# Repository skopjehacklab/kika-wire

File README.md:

Our version of the Little Wire[1] board.

This is a KiCAD project. Pictures of the finished board can be found at : https://i.imgur.com/Hss5jGV.jpg and https://i.imgur.com/ivjp6nn.jpg

[1] - http://littlewire.cc/

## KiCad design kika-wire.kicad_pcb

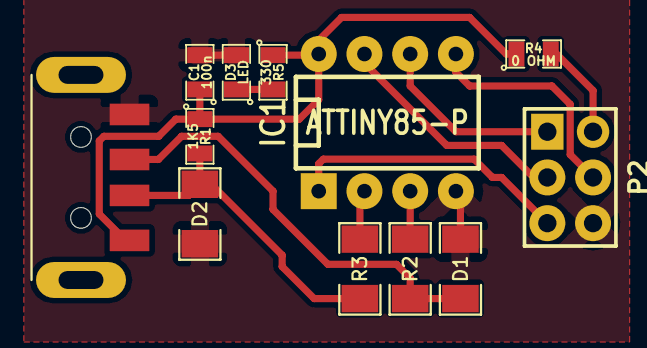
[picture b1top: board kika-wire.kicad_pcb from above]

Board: 2 copper layers, 12 parts (0 on the bottom side), 12 nets.

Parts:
C1: 100n; SM0805
D1, D2: 3V6; SM1206
D3: LED; SM0805
IC1: ATTINY85-P; DIP-8__300
P1: USB-A; USB-A-PLUG-SMT
P2: CONN_3X2; pin_array_3x2
R1: 1K5; SM0805
R2, R3: 68; SM1206
R4: 0 OHM; SM0805
R5: 330; SM0805

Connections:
D+: D1.2, P1.3, R2.1
D-: D2.2, P1.2, R1.2, R3.1
GND: C1.2, D1.1, D2.1, D3.2, IC1.4, P1.4, P2.6
MISO: IC1.6, P2.1
MOSI: IC1.5, P2.4
unnamed: IC1.3, R2.2
unnamed: IC1.2, R3.2
unnamed: D3.1, R5.2
RESET: IC1.1, P2.5
SCK: IC1.7, P2.3
VCC: C1.1, IC1.8, P1.1, R1.1, R4.1, R5.1
VCC_HEADER: P2.2, R4.2

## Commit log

2014-04-21 Added the project
2014-04-21 Added some additional info
